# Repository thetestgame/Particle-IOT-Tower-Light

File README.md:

# Particle-IOT-Tower-Light
<b>V. 1.0.0</b><br/>
Tower Light IOT controller based around the Particle Photon. Designed for the <a href="https://www.adafruit.com/products/2993">Tower Light - Red Yellow Green Alert Light with Buzzer</a> from <a href="adafruit.com">Adafruit</a>.

<hr/>
### Supported Services
* MQTT
* Particle Cloud (Restful and Subscription events)

<hr/>

### Dependencies
 * <a href="https://github.com/hirotakaster/MQTT">MQTT</a>

<hr/>

### MQTT
<b>All feeds respond to the values "ON" for enable and "OFF" for disable</b><br/>
Set the feed value to "" to disable the feed.
* mqttRedLightFeed - Controls the red light pin
* mqttYellowLightFeed - Controls the yellow light pin
* mqttGreenLightFeed - Controls the green light pin
* mqttBuzzerFeed - Controls the buzzer pin
* mqttPowerFeed - Controls the "power" of the device. Sending "OFF" to the feed will prevent the lights from turning on until "ON" is sent (Not currently implemented)

<hr/>
### Particle Cloud
<b>More documentation will be added later!<b/>
<hr/>

### License
<a href="https://github.com/thetestgame/Particle-IOT-Tower-Light/blob/master/LICENSE">MIT</a>

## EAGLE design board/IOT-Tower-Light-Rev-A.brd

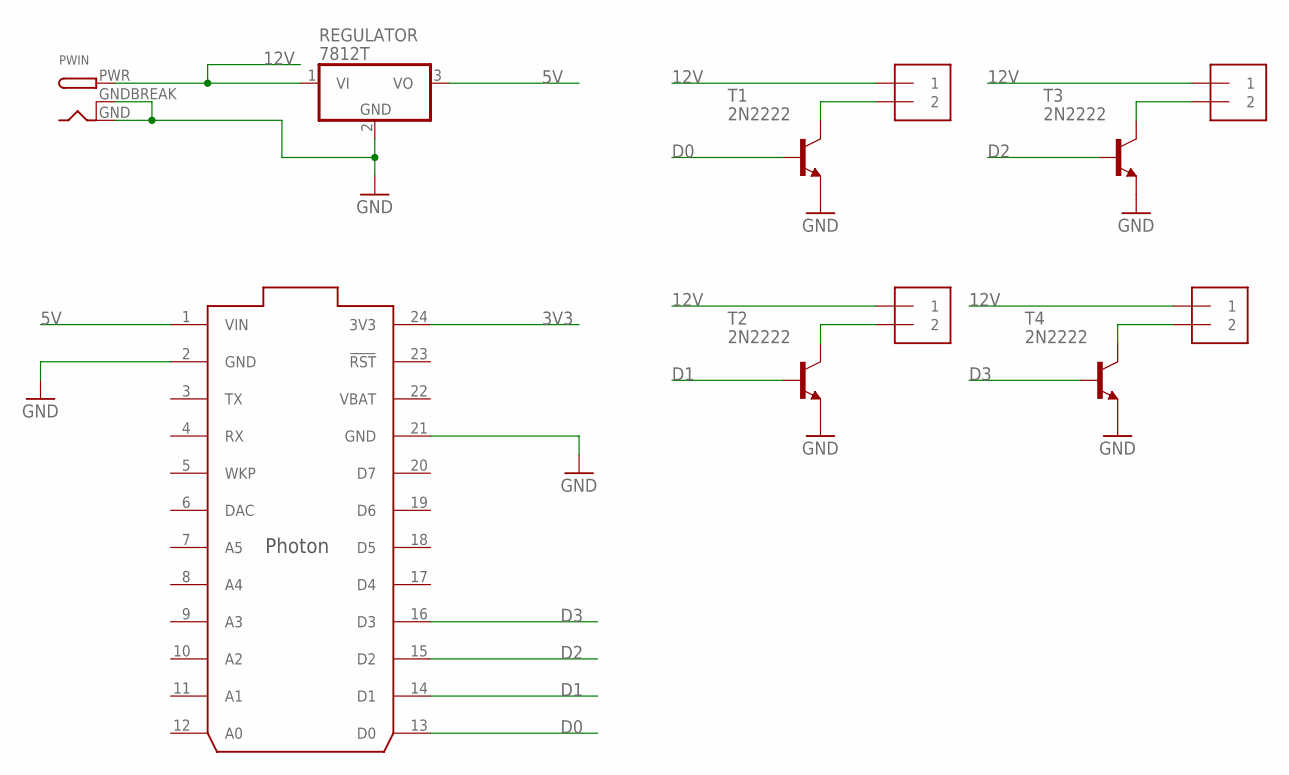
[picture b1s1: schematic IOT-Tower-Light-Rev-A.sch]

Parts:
BUZZER: 1X2-3.5MM
GREEN: 1X2-3.5MM
PWIN: DCBARRELPTH; DCJACK_2MM_PTH
RED: 1X2-3.5MM
REGULATOR: 7812T; TO220H
T1, T2, T3, T4: 2N2222; TO92-EBC-OVAL
U$1: PHOTON_WITH_HEADERS; PHOTON
YELLOW: 1X2-3.5MM

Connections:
3V3: U$1.24 (3V3)
5V: REGULATOR.3 (VO), U$1.1 (VIN)
12V: BUZZER.1, GREEN.1, PWIN.PWR, RED.1, REGULATOR.1 (VI), YELLOW.1
D0: T1.B, U$1.13 (D0)
D1: T2.B, U$1.14 (D1)
D2: T3.B, U$1.15 (D2)
D3: T4.B, U$1.16 (D3)
GND: PWIN.GND, PWIN.GNDBREAK, REGULATOR.2 (GND), T1.E, T2.E, T3.E, T4.E, U$1.2 (GND), U$1.21 (GND)
unnamed: T2.C, YELLOW.2
unnamed: RED.2, T1.C
unnamed: BUZZER.2, T4.C
unnamed: GREEN.2, T3.C
VBAT: U$1.22 (VBAT)

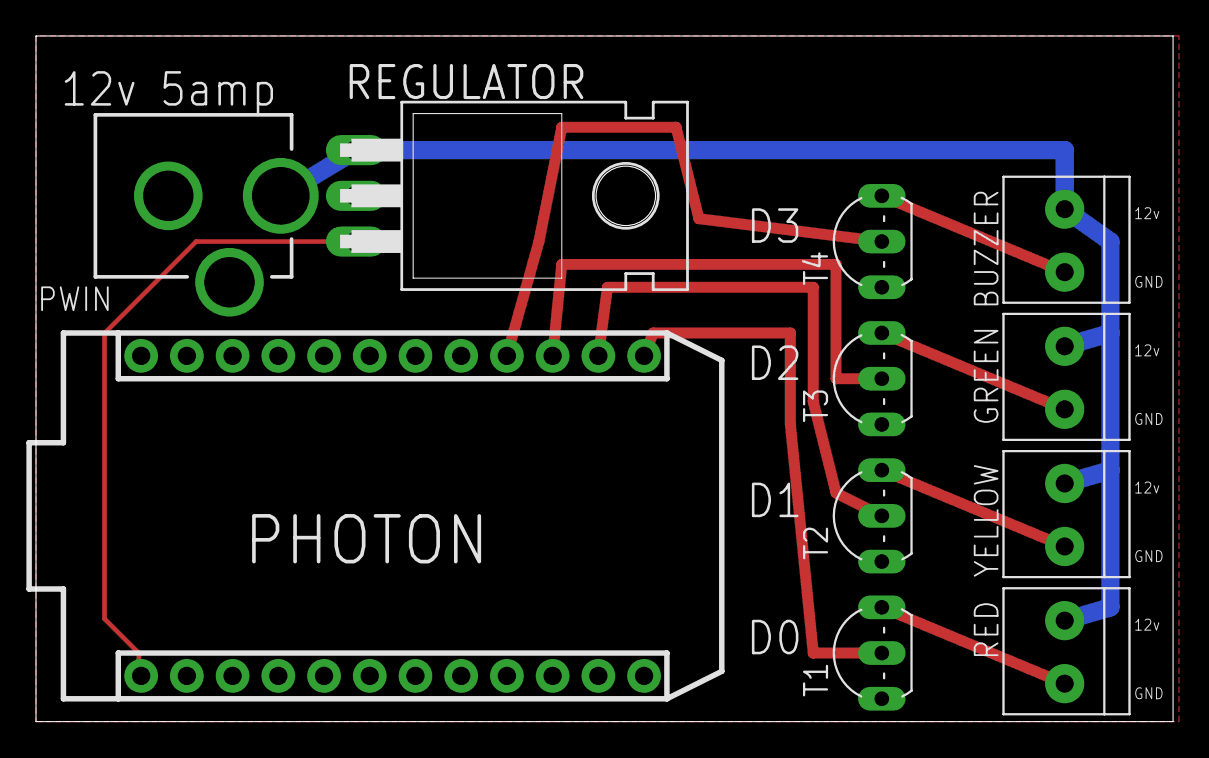
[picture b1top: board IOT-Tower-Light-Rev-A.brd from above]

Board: 2 copper layers, 63.2 x 38.1 mm, 11 parts (0 on the bottom side), 11 nets.

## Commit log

2016-03-23 Added EagleCad design
